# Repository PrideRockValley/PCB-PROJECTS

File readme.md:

<h1 >Rudi 40-Pin Breakout</h1>
<p>As a member of the University of Guelph Robotics Team, I've taken on the exciting challenge of designing a 40-pin breakout board for the Rudi-NX. This marks a significant milestone as my first board design. Leveraging KiCad, I've implemented a PCB breakout for the GPIO Expansion Connector on the Rudi-NX, bringing together various communication protocols and input/output pins.
It is my honor with my teammates.
 </p>
<br>

<h1> Design + 3D Viewer</h1>

<br><br>

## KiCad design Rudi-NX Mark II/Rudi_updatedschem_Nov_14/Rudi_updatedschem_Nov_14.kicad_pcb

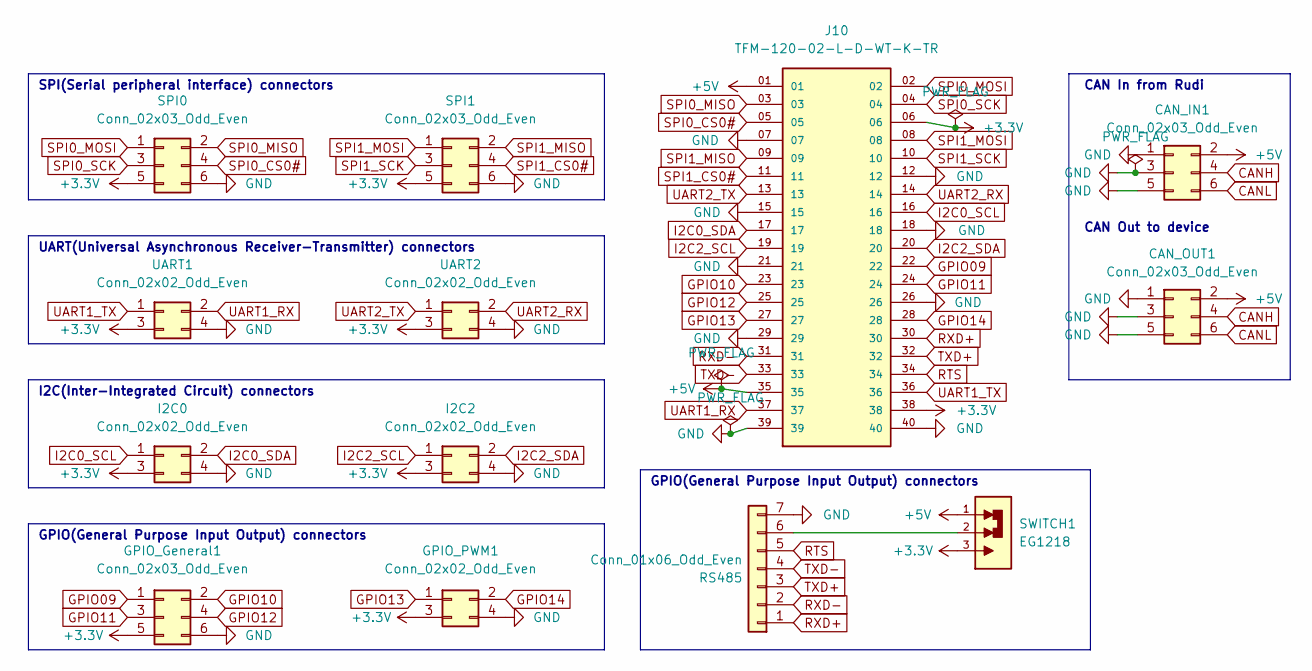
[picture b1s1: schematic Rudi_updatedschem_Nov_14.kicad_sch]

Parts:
CAN_IN1: Conn_02x03_Odd_Even; JST_XH_B6B-XH-A_1x06_P2.50mm_Vertical
CAN_OUT1: Conn_02x03_Odd_Even; JST_XH_B6B-XH-A_1x06_P2.50mm_Vertical
GPIO_General1: Conn_02x03_Odd_Even; JST_XH_B6B-XH-A_1x06_P2.50mm_Vertical
GPIO_PWM1: Conn_02x02_Odd_Even; JST_XH_B4B-XH-A_1x04_P2.50mm_Vertical
I2C0, I2C2: Conn_02x02_Odd_Even; JST_XH_B4B-XH-A_1x04_P2.50mm_Vertical
J10: TFM-120-02-L-D-WT-K-TR; SAMTEC_TFM-120-02-L-D-WT-K-TR; PARTREV Q
RS485: Conn_01x06_Odd_Even; JST_XH_B7B-XH-A_1x07_P2.50mm_Vertical
SPI0, SPI1: Conn_02x03_Odd_Even; JST_XH_B6B-XH-A_1x06_P2.50mm_Vertical
SWITCH1: EG1218; SW_EG1218
UART1, UART2: Conn_02x02_Odd_Even; JST_XH_B4B-XH-A_1x04_P2.50mm_Vertical

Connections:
+3.3V: GPIO_General1.5, GPIO_PWM1.3, I2C0.3, I2C2.3, J10.06, J10.38, SPI0.5, SPI1.5, SWITCH1.3, UART1.3, UART2.3
+5V: CAN_IN1.2, CAN_OUT1.2, J10.01, J10.35, SWITCH1.1
CANH: CAN_IN1.4, CAN_OUT1.4
CANL: CAN_IN1.6, CAN_OUT1.6
GND: CAN_IN1.1, CAN_IN1.3, CAN_IN1.5, CAN_OUT1.1, CAN_OUT1.3, CAN_OUT1.5, GPIO_General1.6, GPIO_PWM1.4, I2C0.4, I2C2.4, J10.07, J10.12, J10.15, J10.18, J10.21, J10.26, J10.29, J10.39, J10.40, RS485.7, SPI0.6, SPI1.6, UART1.4, UART2.4
GPIO09: GPIO_General1.1, J10.22
GPIO10: GPIO_General1.2, J10.23
GPIO11: GPIO_General1.3, J10.24
GPIO12: GPIO_General1.4, J10.25
GPIO13: GPIO_PWM1.1, J10.27
GPIO14: GPIO_PWM1.2, J10.28
I2C0_SCL: I2C0.1, J10.16
I2C0_SDA: I2C0.2, J10.17
I2C2_SCL: I2C2.1, J10.19
I2C2_SDA: I2C2.2, J10.20
unnamed: RS485.6, SWITCH1.2
RTS: J10.34, RS485.5
RXD+: J10.30, RS485.1
RXD-: J10.31, RS485.2
SPI0_CS0#: J10.05, SPI0.4
SPI0_MISO: J10.03, SPI0.2
SPI0_MOSI: J10.02, SPI0.1
SPI0_SCK: J10.04, SPI0.3
SPI1_CS0#: J10.11, SPI1.4
SPI1_MISO: J10.09, SPI1.2
SPI1_MOSI: J10.08, SPI1.1
SPI1_SCK: J10.10, SPI1.3
TXD+: J10.32, RS485.3
TXD-: J10.33, RS485.4
UART1_RX: J10.37, UART1.2
UART1_TX: J10.36, UART1.1
UART2_RX: J10.14, UART2.2
UART2_TX: J10.13, UART2.1

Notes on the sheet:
CAN Out to device
SPI(Serial peripheral interface) connectors
CAN In from Rudi
UART(Universal Asynchronous Receiver-Transmitter) connectors
GPIO(General Purpose Input Output) connectors
I2C(Inter-Integrated Circuit) connectors

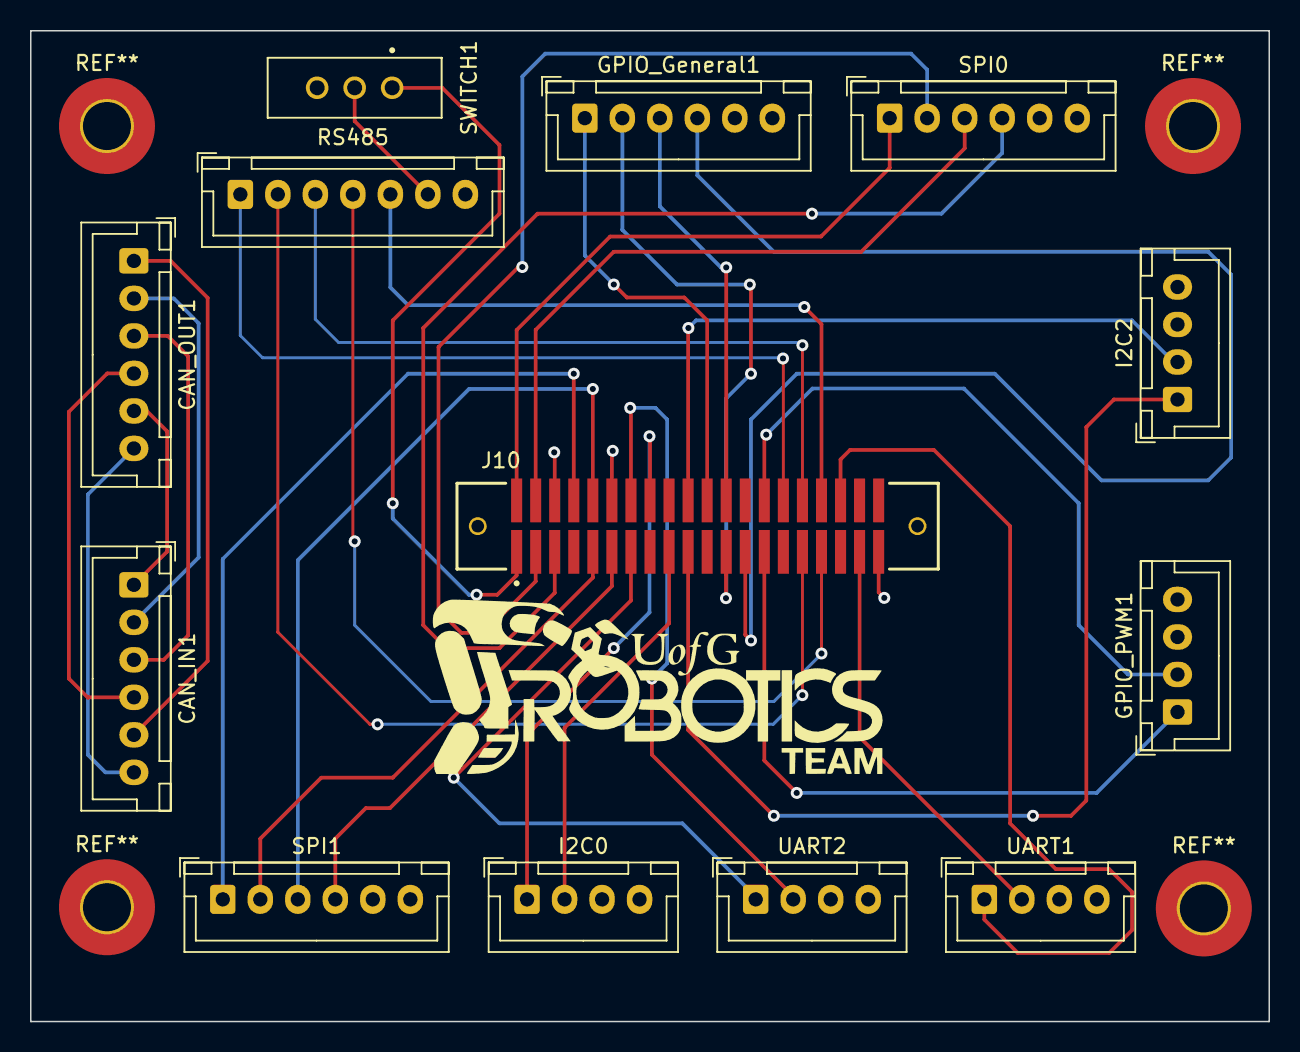
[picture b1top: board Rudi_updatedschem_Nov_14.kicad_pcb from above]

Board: 4 copper layers, 82.6 x 66.0 mm, 13 parts (0 on the bottom side), 33 nets.

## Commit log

2023-12-06 mark II added
2023-12-26 done
2024-01-07 Create new
    new
2024-01-07 Create oh
    oh
2024-01-07 Create op
    pp
2024-01-07 help
2024-01-07 setence
    my feeling
